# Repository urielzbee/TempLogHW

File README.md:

Temperature Logger - Hardware Project

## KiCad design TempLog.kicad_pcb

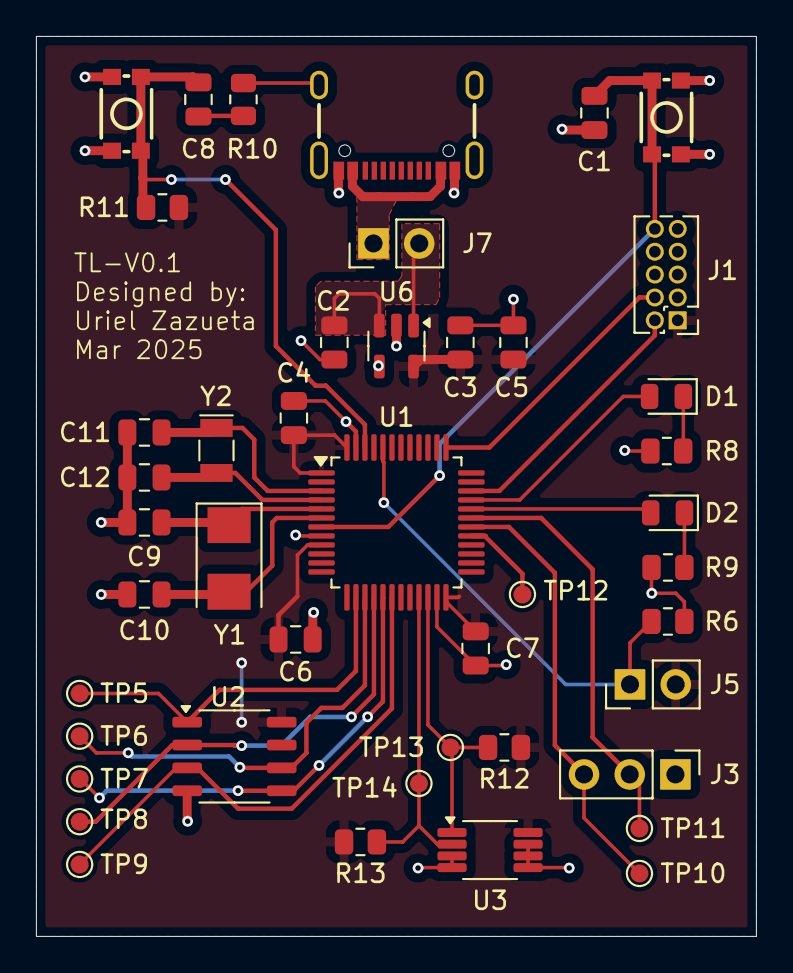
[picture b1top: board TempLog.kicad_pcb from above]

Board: 2 copper layers, 40.0 x 50.0 mm, 44 parts (0 on the bottom side), 28 nets.

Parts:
C1, C2, C3, C4, C5, C6, C7, C8: 100nF; C_0805_2012Metric
C9, C10: 20pF; C_0805_2012Metric
C11, C12: 4.3pF; C_0805_2012Metric
D1: GREEN; LED_0805_2012Metric
D2: RED; LED_0805_2012Metric
J1: 1.27, 2x5, Male, TH; PinHeader_2x05_P1.27mm_Vertical
J3: Conn_01x03; PinHeader_1x03_P2.54mm_Vertical
J5, J7: Conn_01x02; PinHeader_1x02_P2.54mm_Vertical
J6: USB4105-GF-A-060; USB-C_16
R6, R12, R13: 10K; R_0805_2012Metric
R8: 510; R_0805_2012Metric
R9: 330; R_0805_2012Metric
R10, R11: 100; R_0805_2012Metric
SW1, SW2: SMD_4.6x2.8mm_h1.9mm; Push_SMD_4.6x2.8mm_h1.9mm
TP5, TP6, TP7, TP8, TP9, TP10, TP11, TP13, TP14: TestPoint; TestPoint_Pad_D1.0mm
TP12: MCO; TestPoint_Pad_D1.0mm
U1: STM32F030C8Tx; LQFP-48_7x7mm_P0.5mm
U2: GD25Q16CSJGR; SOP-8_3.9x4.9mm_P1.27mm
U3: TMP1075DGK; VSSOP-8_3x3mm_P0.65mm
U6: MIC5504-3.3YM5; SOT-23-5
Y1: 8.0MHz H130A-8.000-18-2030-EXT-TR; Crystal_SMD_5032-2Pin_5.0x3.2mm
Y2: 32.768 KHz CC7V-T1A; Crystal_SMD_MicroCrystal_CC7V-T1A-2Pin_3.2x1.5mm

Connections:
+3V3: C3.1, C4.1, C5.1, C6.1, C7.1, J1.1, J5.2, R11.1, R12.1, R13.1, U1.1 (VDD), U1.9 (VDDA), U1.24 (VDD), U1.48 (VDD), U2.8 (VCC), U3.8 (V+), U6.5 (VOUT)
BOOT0: J5.1, R6.2, U1.44 (BOOT0)
BTN_1: C8.1, R11.2, SW2.2, U1.46 (PB9)
FLASH_MISO: TP8.1, U1.16 (PA6), U2.2 (O1/SO)
FLASH_MOSI: TP7.1, U1.17 (PA7), U2.5 (SI/IO0)
FLASH_SCK: TP6.1, U1.15 (PA5), U2.6 (SCLK)
FLASH_nCS: TP5.1, U1.14 (PA4), U2.1 (~CS)
FLASH_nWP: TP9.1, U1.18 (PB0), U2.3 (~WP)
GND: C1.2, C2.2, C3.2, C4.2, C5.2, C6.2, C7.2, C9.2, C10.2, C11.2, C12.2, J1.3, J1.5, J1.9, J3.1, J6.GND, J6.S (SHIELD), R6.1, R8.1, R9.1, R10.2, SW1.1, SW2.1, U1.8 (VSSA), U1.23 (VSS), U1.47 (VSS), U2.4 (VSS), U3.3 (ALERT), U3.4 (GND), U3.5 (A2), U3.6 (A1), U3.7 (A0), U6.2 (GND)
LED0: D1.2 (A), U1.33 (PA12)
LED1: D2.2 (A), U1.32 (PA11)
NRST: C1.1, J1.10, SW1.2, U1.7 (NRST)
unnamed: C8.2, R10.1
unnamed: D1.1 (K), R8.2
unnamed: D2.1 (K), R9.2
unnamed: TP12.1, U1.29 (PA8)
OSC32_IN: C11.1, U1.3 (PC14), Y2.1
OSC32_OUT: C12.1, U1.4 (PC15), Y2.2
OSC_IN: C9.1, U1.5 (PF0), Y1.1
OSC_OUT: C10.1, U1.6 (PF1), Y1.2
SCL: R13.2, TP14.1, U1.21 (PB10), U3.2 (SCL)
SDA: R12.2, TP13.1, U1.22 (PB11), U3.1 (SDA)
SWDCLK: J1.4, U1.37 (PA14)
SWDIO: J1.2, U1.34 (PA13)
USART1_RX: J3.2, TP11.1, U1.31 (PA10)
USART1_TX: J3.3, TP10.1, U1.30 (PA9)
VBUS: J6.VBUS, J7.1
VCC: C2.1, J7.2, U6.1 (VIN), U6.3 (EN)

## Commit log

2025-01-16 Added PDFs
2025-03-11 Updated project to Kicad 9
2025-03-11 Removed thermistor circuit and added TMP1075 temperature sensor
2025-03-12 updated library links
2025-03-17 Changed board size to 50mm x 40mm and rerouted the nets
2025-03-17 Generated Gerber Files
2025-03-18 Updated BOM. Generated Schematic. Generated Fabrication drawings
